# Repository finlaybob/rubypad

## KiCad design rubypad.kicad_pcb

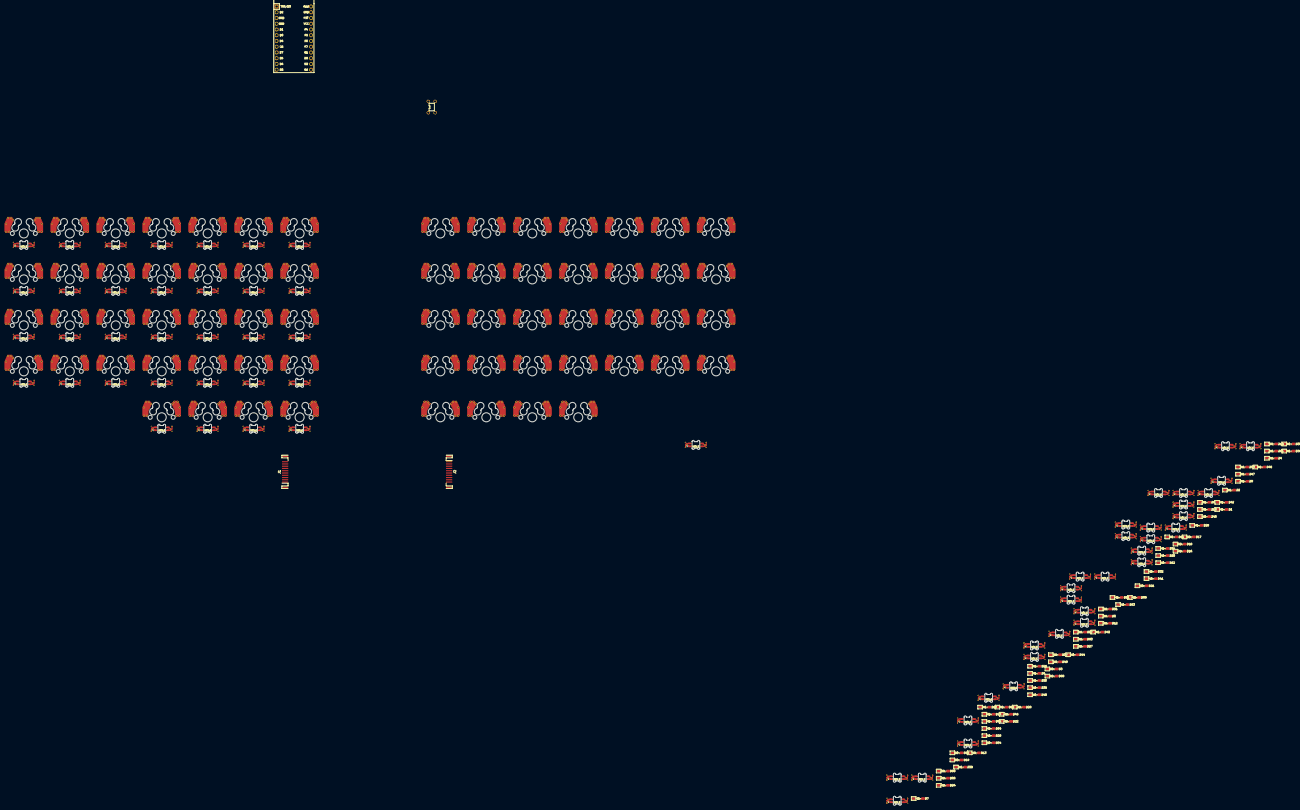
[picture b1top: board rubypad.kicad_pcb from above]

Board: 2 copper layers, 196 parts (0 on the bottom side), 157 nets, no tracks yet.

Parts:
D1, D2, D3, D4, D5, D6, D7, D8, D9, D10, D11, D12, D13, D14, D15, D16, D17, D18, D19, D20, D21, D22, D23, D24, D25, D26, D27, D28, D29, D30, D31, D32, D33, D34, D35, D36, D37, D38, D39, D40, D41, D42, D43, D44, D45, D46, D47, D48, D49, D50, D51, D52, D53, D54, D55, D56, D57, D58, D59, D60, D61, D62, D63, D64: D_Small; D_SOD-123
J1, J2: HDMI_A; HDMI_A_Contact_Technology_HDMI-19APL2_Horizontal
LED1, LED2, LED3, LED4, LED5, LED6, LED7, LED8, LED9, LED10, LED11, LED12, LED13, LED14, LED15, LED16, LED17, LED18, LED19, LED20, LED21, LED22, LED23, LED24, LED25, LED26, LED27, LED28, LED29, LED30, LED31, LED32, LED33, LED34, LED35, LED36, LED37, LED38, LED39, LED40, LED41, LED42, LED43, LED44, LED45, LED46, LED47, LED48, LED49, LED50, LED51, LED52, LED53, LED54, LED55, LED56, LED57, LED58, LED59, LED60, LED61, LED62, LED63, LED64: SK6812Mini-E
SW1, SW2, SW3, SW4, SW5, SW6, SW7, SW8, SW9, SW10, SW11, SW12, SW13, SW14, SW15, SW16, SW17, SW18, SW19, SW20, SW21, SW22, SW23, SW24, SW25, SW26, SW27, SW28, SW29, SW30, SW31, SW32, SW33, SW34, SW35, SW36, SW37, SW38, SW39, SW40, SW41, SW42, SW43, SW44, SW45, SW46, SW47, SW48, SW49, SW50, SW51, SW52, SW53, SW54, SW55, SW56, SW57, SW58, SW59, SW60, SW61, SW62, SW63, SW64: SW_Push; MX-1U-Hotswap
SW65: SW_Push; PushButton_4.5mm
U1: ProMicro; ArduinoProMicro

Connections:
GND: J1.17 (GND), J1.SH, LED1.3 (GND), LED2.3 (GND), LED3.3 (GND), LED4.3 (GND), LED5.3 (GND), LED6.3 (GND), LED7.3 (GND), LED15.3 (GND), LED16.3 (GND), LED17.3 (GND), LED18.3 (GND), LED19.3 (GND), LED20.3 (GND), LED21.3 (GND), LED29.3 (GND), LED30.3 (GND), LED31.3 (GND), LED32.3 (GND), LED33.3 (GND), LED34.3 (GND), LED35.3 (GND), LED43.3 (GND), LED44.3 (GND), LED45.3 (GND), LED46.3 (GND), LED47.3 (GND), LED48.3 (GND), LED49.3 (GND), LED57.3 (GND), LED58.3 (GND), LED59.3 (GND), LED60.3 (GND), SW65.2, U1.3 (GND), U1.4 (GND), U1.22 (RST)
GND_b: J2.17 (GND), J2.SH, LED8.3 (GND), LED9.3 (GND), LED10.3 (GND), LED11.3 (GND), LED12.3 (GND), LED13.3 (GND), LED14.3 (GND), LED22.3 (GND), LED23.3 (GND), LED24.3 (GND), LED25.3 (GND), LED26.3 (GND), LED27.3 (GND), LED28.3 (GND), LED36.3 (GND), LED37.3 (GND), LED38.3 (GND), LED39.3 (GND), LED40.3 (GND), LED41.3 (GND), LED42.3 (GND), LED50.3 (GND), LED51.3 (GND), LED52.3 (GND), LED53.3 (GND), LED54.3 (GND), LED55.3 (GND), LED56.3 (GND), LED61.3 (GND), LED62.3 (GND), LED63.3 (GND), LED64.3 (GND)
LED_DATA_OUT: J1.13 (CEC), LED7.2 (DOUT)
LED_DATA_b: J2.13 (CEC), LED64.4 (DIN)
LED_PWR: J1.15 (SCL), LED1.1 (VDD), LED2.1 (VDD), LED3.1 (VDD), LED4.1 (VDD), LED5.1 (VDD), LED6.1 (VDD), LED7.1 (VDD), LED15.1 (VDD), LED16.1 (VDD), LED17.1 (VDD), LED18.1 (VDD), LED19.1 (VDD), LED20.1 (VDD), LED21.1 (VDD), LED29.1 (VDD), LED30.1 (VDD), LED31.1 (VDD), LED32.1 (VDD), LED33.1 (VDD), LED34.1 (VDD), LED35.1 (VDD), LED43.1 (VDD), LED44.1 (VDD), LED45.1 (VDD), LED46.1 (VDD), LED47.1 (VDD), LED48.1 (VDD), LED49.1 (VDD), LED57.1 (VDD), LED58.1 (VDD), LED59.1 (VDD), LED60.1 (VDD)
LED_PWR_b: J2.15 (SCL), LED8.1 (VDD), LED9.1 (VDD), LED10.1 (VDD), LED11.1 (VDD), LED12.1 (VDD), LED13.1 (VDD), LED14.1 (VDD), LED22.1 (VDD), LED23.1 (VDD), LED24.1 (VDD), LED25.1 (VDD), LED26.1 (VDD), LED27.1 (VDD), LED28.1 (VDD), LED36.1 (VDD), LED37.1 (VDD), LED38.1 (VDD), LED39.1 (VDD), LED40.1 (VDD), LED41.1 (VDD), LED42.1 (VDD), LED50.1 (VDD), LED51.1 (VDD), LED52.1 (VDD), LED53.1 (VDD), LED54.1 (VDD), LED55.1 (VDD), LED56.1 (VDD), LED61.1 (VDD), LED62.1 (VDD), LED63.1 (VDD), LED64.1 (VDD)
unnamed: D1.2 (A), SW1.1
unnamed: D2.2 (A), SW2.1
unnamed: D3.2 (A), SW3.1
unnamed: D4.2 (A), SW4.1
unnamed: D5.2 (A), SW5.1
unnamed: D6.2 (A), SW6.1
unnamed: D7.2 (A), SW7.1
unnamed: D8.2 (A), SW8.1
unnamed: D9.2 (A), SW9.1
unnamed: D10.2 (A), SW10.1
unnamed: D11.2 (A), SW11.1
unnamed: D12.2 (A), SW12.1
unnamed: D13.2 (A), SW13.1
unnamed: D14.2 (A), SW14.1
unnamed: D15.2 (A), SW15.1
unnamed: D16.2 (A), SW16.1
unnamed: D17.2 (A), SW17.1
unnamed: D18.2 (A), SW18.1
unnamed: D19.2 (A), SW19.1
unnamed: D20.2 (A), SW20.1
unnamed: D21.2 (A), SW21.1
unnamed: D22.2 (A), SW22.1
unnamed: D23.2 (A), SW23.1
unnamed: D24.2 (A), SW24.1
unnamed: D25.2 (A), SW25.1
unnamed: D26.2 (A), SW26.1
unnamed: D27.2 (A), SW27.1
unnamed: D28.2 (A), SW28.1
unnamed: D29.2 (A), SW29.1
unnamed: D30.2 (A), SW30.1
unnamed: D31.2 (A), SW31.1
unnamed: D32.2 (A), SW32.1
unnamed: D33.2 (A), SW33.1
unnamed: D34.2 (A), SW34.1
unnamed: D35.2 (A), SW35.1
unnamed: D36.2 (A), SW36.1
unnamed: D37.2 (A), SW37.1
unnamed: D38.2 (A), SW38.1
unnamed: D39.2 (A), SW39.1
unnamed: D40.2 (A), SW40.1
unnamed: D41.2 (A), SW41.1
unnamed: D42.2 (A), SW42.1
unnamed: D43.2 (A), SW43.1
unnamed: D44.2 (A), SW44.1
unnamed: D45.2 (A), SW45.1
unnamed: D46.2 (A), SW46.1
unnamed: D47.2 (A), SW47.1
unnamed: D48.2 (A), SW48.1
unnamed: D49.2 (A), SW49.1
unnamed: D50.2 (A), SW50.1
unnamed: D51.2 (A), SW51.1
unnamed: D52.2 (A), SW52.1
unnamed: D53.2 (A), SW53.1
unnamed: D54.2 (A), SW54.1
unnamed: D55.2 (A), SW55.1
unnamed: D56.2 (A), SW56.1
unnamed: D57.2 (A), SW57.1
unnamed: D58.2 (A), SW58.1
unnamed: D59.2 (A), SW59.1
unnamed: D60.2 (A), SW60.1
unnamed: D61.2 (A), SW61.1
unnamed: D62.2 (A), SW62.1
unnamed: D63.2 (A), SW63.1
unnamed: D64.2 (A), SW64.1
unnamed: LED1.2 (DOUT), LED2.4 (DIN)
unnamed: LED1.4 (DIN), LED15.2 (DOUT)
unnamed: LED2.2 (DOUT), LED3.4 (DIN)
unnamed: LED3.2 (DOUT), LED4.4 (DIN)
unnamed: LED4.2 (DOUT), LED5.4 (DIN)
unnamed: LED5.2 (DOUT), LED6.4 (DIN)
unnamed: LED6.2 (DOUT), LED7.4 (DIN)
unnamed: LED8.4 (DIN), LED9.2 (DOUT)
unnamed: LED9.4 (DIN), LED10.2 (DOUT)
unnamed: LED10.4 (DIN), LED11.2 (DOUT)
unnamed: LED11.4 (DIN), LED12.2 (DOUT)
unnamed: LED12.4 (DIN), LED13.2 (DOUT)
unnamed: LED13.4 (DIN), LED14.2 (DOUT)
unnamed: LED14.4 (DIN), LED28.2 (DOUT)
unnamed: LED15.4 (DIN), LED16.2 (DOUT)
unnamed: LED16.4 (DIN), LED17.2 (DOUT)
unnamed: LED17.4 (DIN), LED18.2 (DOUT)
unnamed: LED18.4 (DIN), LED19.2 (DOUT)
unnamed: LED19.4 (DIN), LED20.2 (DOUT)
unnamed: LED20.4 (DIN), LED21.2 (DOUT)
unnamed: LED21.4 (DIN), LED35.2 (DOUT)
unnamed: LED22.2 (DOUT), LED23.4 (DIN)
unnamed: LED22.4 (DIN), LED36.2 (DOUT)
unnamed: LED23.2 (DOUT), LED24.4 (DIN)
unnamed: LED24.2 (DOUT), LED25.4 (DIN)
unnamed: LED25.2 (DOUT), LED26.4 (DIN)
unnamed: LED26.2 (DOUT), LED27.4 (DIN)
unnamed: LED27.2 (DOUT), LED28.4 (DIN)
unnamed: LED29.2 (DOUT), LED30.4 (DIN)
unnamed: LED29.4 (DIN), LED43.2 (DOUT)
unnamed: LED30.2 (DOUT), LED31.4 (DIN)
unnamed: LED31.2 (DOUT), LED32.4 (DIN)
unnamed: LED32.2 (DOUT), LED33.4 (DIN)
unnamed: LED33.2 (DOUT), LED34.4 (DIN)
unnamed: LED34.2 (DOUT), LED35.4 (DIN)
unnamed: LED36.4 (DIN), LED37.2 (DOUT)
unnamed: LED37.4 (DIN), LED38.2 (DOUT)
unnamed: LED38.4 (DIN), LED39.2 (DOUT)
unnamed: LED39.4 (DIN), LED40.2 (DOUT)
unnamed: LED40.4 (DIN), LED41.2 (DOUT)
unnamed: LED41.4 (DIN), LED42.2 (DOUT)
unnamed: LED42.4 (DIN), LED56.2 (DOUT)
unnamed: LED43.4 (DIN), LED44.2 (DOUT)
unnamed: LED44.4 (DIN), LED45.2 (DOUT)
unnamed: LED45.4 (DIN), LED46.2 (DOUT)
unnamed: LED46.4 (DIN), LED47.2 (DOUT)
unnamed: LED47.4 (DIN), LED48.2 (DOUT)
unnamed: LED48.4 (DIN), LED49.2 (DOUT)
unnamed: LED49.4 (DIN), LED60.2 (DOUT)
unnamed: LED50.2 (DOUT), LED51.4 (DIN)
unnamed: LED50.4 (DIN), LED61.2 (DOUT)
unnamed: LED51.2 (DOUT), LED52.4 (DIN)
unnamed: LED52.2 (DOUT), LED53.4 (DIN)
unnamed: LED53.2 (DOUT), LED54.4 (DIN)
unnamed: LED54.2 (DOUT), LED55.4 (DIN)
unnamed: LED55.2 (DOUT), LED56.4 (DIN)
unnamed: LED57.2 (DOUT), LED58.4 (DIN)
unnamed: LED58.2 (DOUT), LED59.4 (DIN)
unnamed: LED59.2 (DOUT), LED60.4 (DIN)
unnamed: LED61.4 (DIN), LED62.2 (DOUT)
unnamed: LED62.4 (DIN), LED63.2 (DOUT)
unnamed: LED63.4 (DIN), LED64.2 (DOUT)
unnamed: SW65.1, U1.23 (GND)
col0: SW1.2, SW15.2, SW29.2, SW43.2
col1: SW2.2, SW16.2, SW30.2, SW44.2
col2: SW3.2, SW17.2, SW31.2, SW45.2
col3: SW4.2, SW18.2, SW32.2, SW46.2, SW57.2
col4: SW5.2, SW19.2, SW33.2, SW47.2, SW58.2
col5: SW6.2, SW20.2, SW34.2, SW48.2, SW59.2
col6: SW7.2, SW21.2, SW35.2, SW49.2, SW60.2
col7_b: J2.1 (D2+), SW8.2, SW22.2, SW36.2, SW50.2, SW61.2
col8_b: J2.3 (D2-), SW9.2, SW23.2, SW37.2, SW51.2, SW62.2
col9_b: J2.4 (D1+), SW10.2, SW24.2, SW38.2, SW52.2, SW63.2
col10_b: J2.6 (D1-), SW11.2, SW25.2, SW39.2, SW53.2, SW64.2
col11_b: J2.7 (D0+), SW12.2, SW26.2, SW40.2, SW54.2
col12_b: J2.9 (D0-), SW13.2, SW27.2, SW41.2, SW55.2
col13_b: J2.10 (CK+), SW14.2, SW28.2, SW42.2, SW56.2
row0: D1.1 (K), D2.1 (K), D3.1 (K), D4.1 (K), D5.1 (K), D6.1 (K), D7.1 (K), J1.2 (D2S)
row0_b: D8.1 (K), D9.1 (K), D10.1 (K), D11.1 (K), D12.1 (K), D13.1 (K), D14.1 (K), J2.2 (D2S)
row1: D15.1 (K), D16.1 (K), D17.1 (K), D18.1 (K), D19.1 (K), D20.1 (K), D21.1 (K), J1.5 (D1S)
row1_b: D22.1 (K), D23.1 (K), D24.1 (K), D25.1 (K), D26.1 (K), D27.1 (K), D28.1 (K), J2.5 (D1S)
row2: D29.1 (K), D30.1 (K), D31.1 (K), D32.1 (K), D33.1 (K), D34.1 (K), D35.1 (K), J1.8 (D0S)
row2_b: D36.1 (K), D37.1 (K), D38.1 (K), D39.1 (K), D40.1 (K), D41.1 (K), D42.1 (K), J2.8 (D0S)
row3: D43.1 (K), D44.1 (K), D45.1 (K), D46.1 (K), D47.1 (K), D48.1 (K), D49.1 (K), J1.11 (CKS)
row3_b: D50.1 (K), D51.1 (K), D52.1 (K), D53.1 (K), D54.1 (K), D55.1 (K), D56.1 (K), J2.11 (CKS)
row4: D57.1 (K), D58.1 (K), D59.1 (K), D60.1 (K), J1.19 (HPD)
row4_b: D61.1 (K), D62.1 (K), D63.1 (K), D64.1 (K), J2.19 (HPD)

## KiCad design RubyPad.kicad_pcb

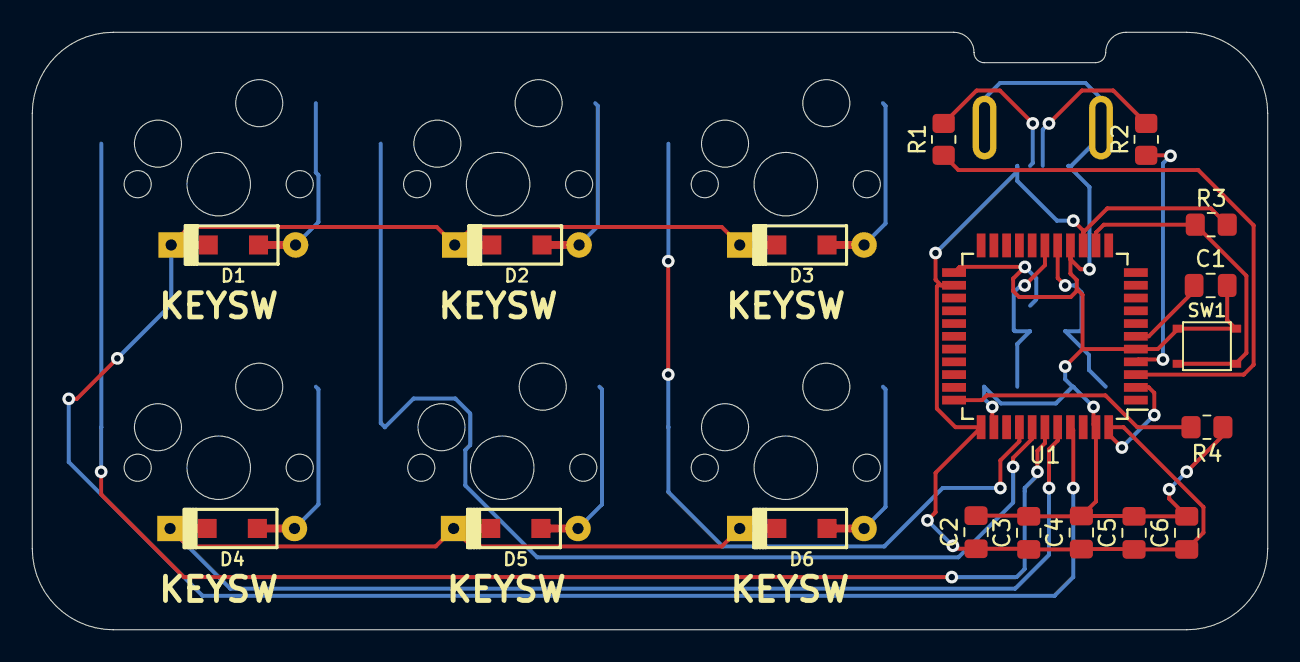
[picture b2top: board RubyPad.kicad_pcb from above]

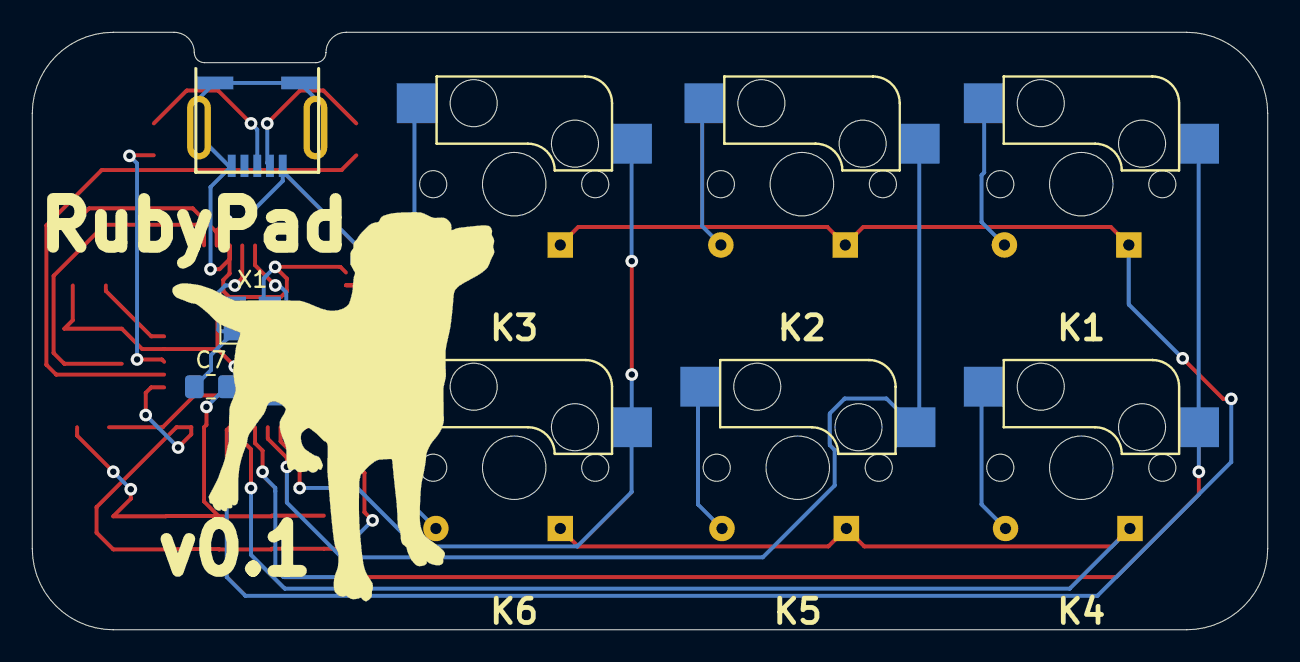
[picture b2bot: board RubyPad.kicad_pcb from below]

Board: 2 copper layers, 77.5 x 37.5 mm, 28 parts (10 on the bottom side), 22 nets.

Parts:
C1: 1u; C_0805_2012Metric_Pad1.18x1.45mm_HandSolder
C2, C3, C4, C5: 0.1u; C_0805_2012Metric_Pad1.18x1.45mm_HandSolder
C6: 4.7u; C_0805_2012Metric_Pad1.18x1.45mm_HandSolder
C7, C8: 22p; C_0805_2012Metric_Pad1.18x1.45mm_HandSolder
D1, D2, D3, D4, D5, D6: D; D_SOD123_axial
J1: USB_mini_micro_B; USB_miniB_hirose_5S8
K1, K2, K3, K4, K5, K6: KEYSW; Kailh_MX_Socket
R1, R2: 22; R_0805_2012Metric_Pad1.20x1.40mm_HandSolder
R3, R4: 10k; R_0805_2012Metric_Pad1.20x1.40mm_HandSolder
SW1: SW_PUSH; SW_SPST_3x3
U1: ATMEGA32U4; TQFP-44_10x10mm_P0.8mm
X1: XTAL_GND; Crystal_SMD_SeikoEpson_TSX3225-4Pin_3.2x2.5mm

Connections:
/col0: K1.1, K4.1, U1.39
/col1: K2.1, K5.1, U1.38
/col2: K3.1, K6.1, U1.37
/row0: D1.1, D2.1, D3.1, U1.41
/row1: D4.1, D5.1, D6.1, U1.40
GND: C1.2, C2.2, C3.2, C4.2, C5.2, C6.2, C7.2, C8.2, J1.5, J1.6, R4.1, SW1.1, U1.5, U1.15, U1.23, U1.35, U1.43, X1.3
unnamed: C1.1, U1.6
unnamed: C7.1, U1.16, X1.1
unnamed: C8.1, U1.17, X1.2
unnamed: D1.2, K1.2
unnamed: D2.2, K2.2
unnamed: D3.2, K3.2
unnamed: D4.2, K4.2
unnamed: D5.2, K5.2
unnamed: D6.2, K6.2
unnamed: J1.2, R1.2
unnamed: J1.3, R2.2
unnamed: R1.1, U1.3
unnamed: R2.1, U1.4
unnamed: R3.1, SW1.2, U1.13
unnamed: R4.2, U1.33
VCC: C2.1, C3.1, C4.1, C5.1, C6.1, J1.1, R3.2, U1.2, U1.14, U1.24, U1.34, U1.44

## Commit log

2021-12-20 Initialise
2021-12-20 Add Files
2021-12-23 saved
2021-12-23 Redone the pcb again but forgot the 'fill area' thing
2022-01-07 starting over from scratch with different guide
2022-01-07 add blank project
2022-01-07 Add submodules
2022-01-07 adding libs
2022-01-07 add module that (hopefully) has an elite-c
2022-01-07 add submodule for components
2022-01-11 save changes
2022-01-11 Setup encoder schematic
2022-01-11 Update - ran traces
2022-01-12 Added 3d models
2022-01-12 backups
2022-01-13 remove
2022-01-15 Adding tzarcs reversible stuff
2022-01-16 rev2 is rev1
2022-04-07 Something weird happened
2022-04-12 resuming works
2022-04-12 adding new parts
2022-04-12 add to schematic
2022-04-12 changes and complete
2022-04-14 udpate - going to redo pcb again
2022-04-14 udpate
